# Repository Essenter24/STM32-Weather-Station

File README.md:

# Weather Station STM32

An embedded weather station based on STM32 with self developed PCB engineered using KiCad. 

The system, as for now, offers measurements of humidity, pressure and temperature with simple moving average filtering, 
alongside visualizing the data on LCD screen based on HD44780 controller, as well as sending data in JSON format by UART transmission

## Main Functions
* **Measurements**
  * Temperature, humidity and pressure (BME690)
* **Visualization**
  * LCD 2x16 based on HD44780 controller
  * Brightness set either manually or automatically, based on light level (measured by photoresistor)
* **Connectivity**
  * UART DMA communication for sending data in JSON format
 
## Hardware
* Custom-designed PCB developed in KiCad
* MCU: STM32L476RG6
* Weather sensor: BME690

## Future plans
* Handling air quality control with BME690
* Moving the entire architecture to RTOS
* Improve UART communication reliability during LCD updates

## Known issues
* UART tends to send garbage data when the LCD is being refreshed - a flag is used to omit the refreshement of LCD when UART is being transmitted

## Project status
Project is under active development

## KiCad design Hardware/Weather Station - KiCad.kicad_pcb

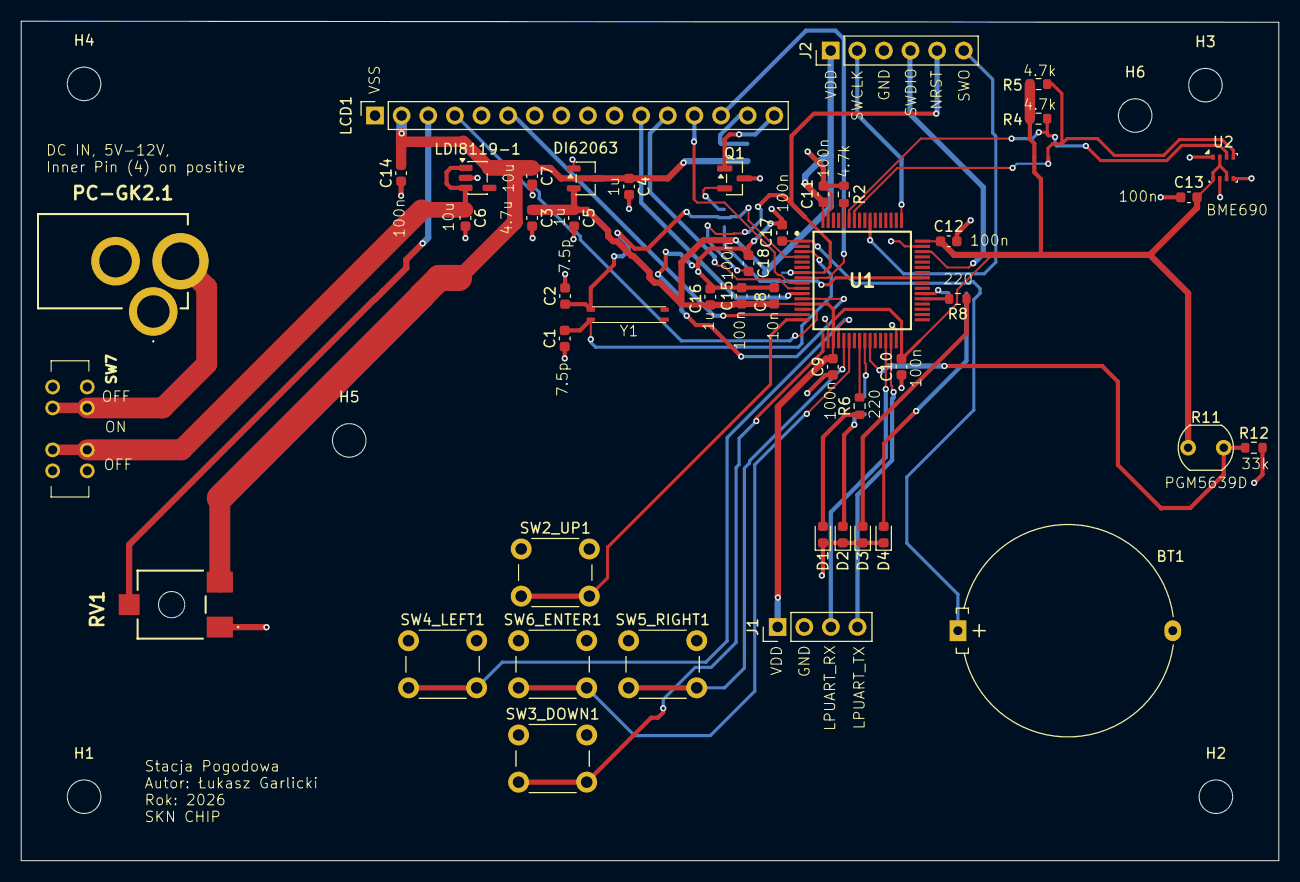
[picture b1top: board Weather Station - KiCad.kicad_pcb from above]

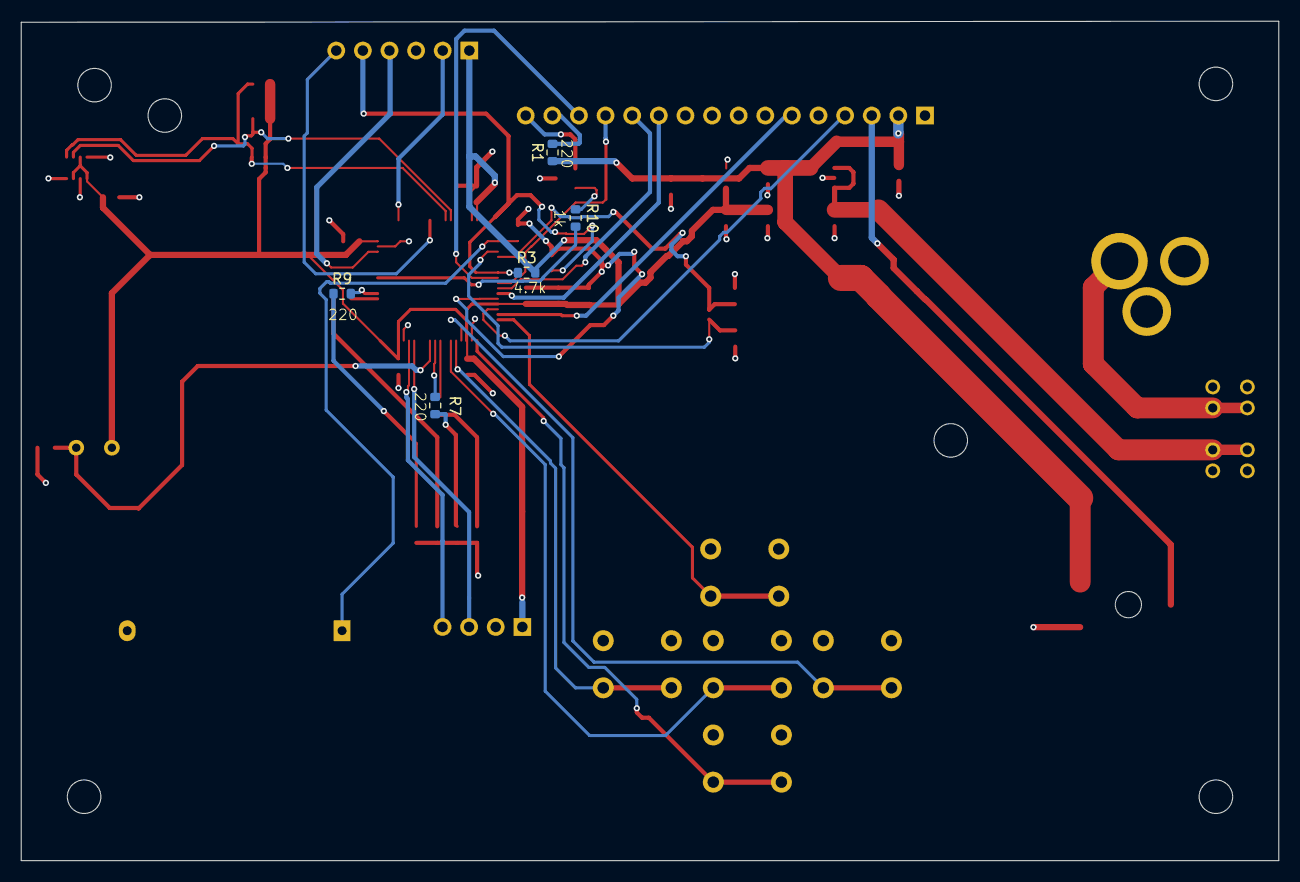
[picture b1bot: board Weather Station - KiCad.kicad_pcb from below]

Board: 4 copper layers, 120.0 x 80.1 mm, 58 parts (5 on the bottom side), 42 nets.

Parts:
BT1: CR2032; Battery_Panasonic_CR2032-HFN_Horizontal_CircularHoles
C1, C2: 7.5p; C_0603_1608Metric
C3: 4.7u; C_0603_1608Metric
C4, C5, C16: 1u; C_0603_1608Metric
C6, C7: 10u; C_0603_1608Metric
C8: 10n; C_0603_1608Metric
C9, C10, C11, C12, C13, C14, C15, C17, C18: 100n; C_0603_1608Metric
D1, D2, D3, D4: LED; LED_0603_1608Metric
DI62063: SOT-23-3
H1, H2, H3, H4, H5, H6: MountingHole; MountingHole_3.2mm_M3
J1: Conn_01x04_Pin; PinHeader_1x04_P2.54mm_Vertical
J2: Conn_01x06_Pin; PinHeader_1x06_P2.54mm_Vertical
LCD1: PinSocket_1x16_P2.54mm_Vertical
LDI8119-1: SOT-23-5
PC-GK2.1: PCGK21
Q1: MMBT3904; SOT-23
R1, R6, R7, R8, R9: 220; R_0603_1608Metric
R2, R3, R4, R5: 4.7k; R_0603_1608Metric
R10: 1k; R_0603_1608Metric
R11: PGM5639D; R_LDR_5.1x4.3mm_P3.4mm_Vertical
R12: 33k; R_0603_1608Metric
RV1: CA6XVSMD; CA6XVSMD10KA2525
SW2_UP1, SW3_DOWN1, SW4_LEFT1, SW5_RIGHT1, SW6_ENTER1: SW_Push; SW_PUSH_6mm_H5mm
SW7: SW_Slide_DPDT; MSS2346
U1: STM32L476RGT6
U2: BME690; Bosch_LGA-8_2.5x2.5mm_P0.65mm_ClockwisePinNumbering
Y1: QT1M-32.768KDZF-T; QT1M

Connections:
+3.3V: C3.1, C5.1, C8.2, C9.2, C10.2, C11.2, C12.1, C13.2, C15.2, C16.2, DI62063.2 (Vout), J1.1, J2.1, R3.2, R4.1, R5.1, R11.1, U1.13 (VDDA/VREF+), U1.19 (VDD@19), U1.32 (VDD@32), U1.48 (VDDUSB), U1.64 (VDD@64), U2.2 (CSB), U2.6 (VDDIO), U2.8 (VDD)
+5V: C4.1, C7.1, C14.2, DI62063.3 (Vin), LCD1.2 (VDD), LDI8119-1.5 (Vout), R1.1, RV1.3
GND: BT1.2 (-), C1.1, C2.2, C3.2, C4.2, C5.2, C6.2, C7.2, C8.1, C9.1, C10.1, C11.1, C12.2, C13.1, C14.1, C15.1, C16.1, C17.1, C18.1, D1.1 (K), D2.1 (K), D3.1 (K), D4.1 (K), DI62063.1 (Vss), J1.2, J2.3, LCD1.1 (VSS), LCD1.5 (R/W), LDI8119-1.2 (GND), PC-GK2.1.2 (GND), PC-GK2.1.3 (GND), Q1.3 (E), R2.2, R12.2, RV1.1, SW2_UP1.1, SW3_DOWN1.1, SW4_LEFT1.1, SW5_RIGHT1.1, SW6_ENTER1.1, U1.12 (VSSA/VREF-), U1.18 (VSS@18), U1.31 (VSS@31), U1.47 (VSS@47), U1.63 (VSS@63), U2.1 (GND), U2.5 (SDO), U2.7 (GND)
unnamed: BT1.1 (+), C17.2, U1.1 (VBAT)
unnamed: D1.2 (A), R6.1
unnamed: D2.2 (A), R7.1
unnamed: D3.2 (A), R8.1
unnamed: D4.2 (A), R9.1
unnamed: J1.3, U1.29 (PB10)
unnamed: J1.4, U1.30 (PB11)
unnamed: J2.2, U1.49 (PA14(JTCK-SWCLK))
unnamed: J2.4, U1.46 (PA13(JTMS-SWDIO))
unnamed: C18.2, J2.5, R3.1, U1.7 (NRST)
unnamed: J2.6, U1.55 (PB3(JTDO-TRACESWO))
unnamed: LCD1.11 (DB4), U1.11 (PC3)
unnamed: LCD1.12 (DB5), U1.10 (PC2)
unnamed: LCD1.13 (DB6), U1.9 (PC1)
unnamed: LCD1.14 (DB7), U1.8 (PC0)
unnamed: LCD1.6 (E), U1.15 (PA1)
unnamed: LCD1.15 (LEDA), R1.2
unnamed: LCD1.16 (LEDK), Q1.1 (C)
unnamed: LCD1.4 (RS), U1.14 (PA0)
unnamed: LCD1.3 (V0), RV1.2
unnamed: C6.1, LDI8119-1.1 (Vin), LDI8119-1.3 (EN), SW7.3 (C), SW7.6 (A)
unnamed: PC-GK2.1.4 (V), SW7.2 (B), SW7.7 (B)
unnamed: Q1.2 (B), R10.2
unnamed: R2.1, U1.60 (BOOT0)
unnamed: SW2_UP1.2, U1.16 (PA2)
unnamed: SW3_DOWN1.2, U1.17 (PA3)
unnamed: SW4_LEFT1.2, U1.20 (PA4)
unnamed: SW5_RIGHT1.2, U1.21 (PA5)
unnamed: SW6_ENTER1.2, U1.22 (PA6)
unnamed: R10.1, U1.41 (PA8)
unnamed: R11.2, R12.1, U1.26 (PB0)
unnamed: R5.2, U1.58 (PB6), U2.4 (SCK)
unnamed: R4.2, U1.59 (PB7), U2.3 (SDI)
unnamed: R6.2, U1.24 (PC4)
unnamed: R7.2, U1.25 (PC5)
unnamed: R8.2, U1.37 (PC6)
unnamed: R9.2, U1.38 (PC7)
unnamed: C1.2, U1.3 (PC14-OSC32_IN(PC14)), Y1.4 (2)
unnamed: C2.1, U1.4 (PC15-OSC32_OUT(PC15)), Y1.1

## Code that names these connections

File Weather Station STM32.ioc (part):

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Mcu.Name=STM32L476R(C-E-G)Tx
Mcu.Package=LQFP64
Mcu.UserName=STM32L476RGTx
PA0.GPIOParameters=GPIO_Label
PA0.GPIO_Label=LCD_RS
PA0.Signal=GPIO_Output
PA1.GPIOParameters=GPIO_Label
PA1.GPIO_Label=LCD_E
PA1.Signal=GPIO_Output
PA13\ (JTMS-SWDIO).Mode=Serial_Wire
PA13\ (JTMS-SWDIO).Signal=SYS_JTMS-SWDIO
PA14\ (JTCK-SWCLK).Mode=Serial_Wire
PA14\ (JTCK-SWCLK).Signal=SYS_JTCK-SWCLK
PA2.GPIOParameters=GPIO_PuPd,GPIO_Label,GPIO_ModeDefaultEXTI
PA2.GPIO_Label=SW2_UP
PA2.GPIO_ModeDefaultEXTI=GPIO_MODE_IT_RISING
PA2.GPIO_PuPd=GPIO_PULLUP
PA2.Signal=GPXTI2
PA3.GPIOParameters=GPIO_PuPd,GPIO_Label,GPIO_ModeDefaultEXTI
PA3.GPIO_Label=SW3_DOWN
PA3.GPIO_ModeDefaultEXTI=GPIO_MODE_IT_RISING
PA3.GPIO_PuPd=GPIO_PULLUP
PA3.Signal=GPXTI3
PA4.GPIOParameters=GPIO_PuPd,GPIO_Label,GPIO_ModeDefaultEXTI
PA4.GPIO_Label=SW4_LEFT
PA4.GPIO_ModeDefaultEXTI=GPIO_MODE_IT_RISING
PA4.GPIO_PuPd=GPIO_PULLUP
PA4.Signal=GPXTI4
PA5.GPIOParameters=GPIO_PuPd,GPIO_Label
PA5.GPIO_Label=SW5_RIGHT
PA5.GPIO_PuPd=GPIO_PULLUP
PA5.Signal=GPXTI5
PA6.GPIOParameters=GPIO_PuPd,GPIO_Label
PA6.GPIO_Label=SW6_ENTER
PA6.GPIO_PuPd=GPIO_PULLUP
PA6.Signal=GPXTI6
PA8.Signal=S_TIM1_CH1
PB0.GPIOParameters=GPIO_Label
PB0.GPIO_Label=ADC
PB0.Signal=ADCx_IN15
PB10.GPIOParameters=GPIO_Label
PB10.GPIO_Label=UART_RX
PB10.Mode=Asynchronous
PB10.Signal=LPUART1_RX
PB11.GPIOParameters=GPIO_Label
PB11.GPIO_Label=UART_TX
PB11.Mode=Asynchronous
PB11.Signal=LPUART1_TX
PB6.GPIOParameters=GPIO_Speed,GPIO_FM6,GPIO_Label,GPIO_Pu,GPIO_Mode
PB6.GPIO_FM6=__NULL
PB6.GPIO_Label=BME690_SCL
PB6.GPIO_Mode=GPIO_MODE_AF_OD
PB6.GPIO_Pu=GPIO_NOPULL
PB6.GPIO_Speed=GPIO_SPEED_FREQ_VERY_HIGH
PB6.Mode=I2C
PB6.Signal=I2C1_SCL
PB7.GPIOParameters=GPIO_Speed,GPIO_Label,GPIO_Pu,GPIO_FM7,GPIO_Mode
PB7.GPIO_FM7=__NULL
PB7.GPIO_Label=BME690_SDA
PB7.GPIO_Mode=GPIO_MODE_AF_OD
PB7.GPIO_Pu=GPIO_NOPULL
PB7.GPIO_Speed=GPIO_SPEED_FREQ_VERY_HIGH
PB7.Mode=I2C
PB7.Signal=I2C1_SDA
PC0.GPIOParameters=GPIO_Label
PC0.GPIO_Label=LCD_DB7
PC0.Signal=GPIO_Output
PC1.GPIOParameters=GPIO_Label
PC1.GPIO_Label=LCD_DB6
PC1.Signal=GPIO_Output
PC14-OSC32_IN\ (PC14).Mode=LSE-External-Oscillator
PC14-OSC32_IN\ (PC14).Signal=RCC_OSC32_IN
PC15-OSC32_OUT\ (PC15).Mode=LSE-External-Oscillator
PC15-OSC32_OUT\ (PC15).Signal=RCC_OSC32_OUT
PC2.GPIOParameters=GPIO_Label
PC2.GPIO_Label=LCD_DB5
PC2.Signal=GPIO_Output
PC3.GPIOParameters=GPIO_Label
PC3.GPIO_Label=LCD_DB4
PC3.Signal=GPIO_Output
PC4.GPIOParameters=GPIO_Label
PC4.GPIO_Label=D1
PC4.Signal=GPIO_Output
PC5.GPIOParameters=GPIO_Label
PC5.GPIO_Label=D2
PC5.Signal=GPIO_Output
PC6.GPIOParameters=GPIO_Label
PC6.GPIO_Label=D3
PC6.Signal=GPIO_Output
PC7.GPIOParameters=GPIO_Label
PC7.GPIO_Label=D4
PC7.Signal=GPIO_Output
RCC.HSE_VALUE=8000000
RCC.SYSCLKFreq_VALUE=80000000
RCC.SYSCLKSource=RCC_SYSCLKSOURCE_PLLCLK
board=custom
